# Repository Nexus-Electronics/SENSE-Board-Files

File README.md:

# SENSE-Board-Files

This repository contains the EAGLE files for SENSE.

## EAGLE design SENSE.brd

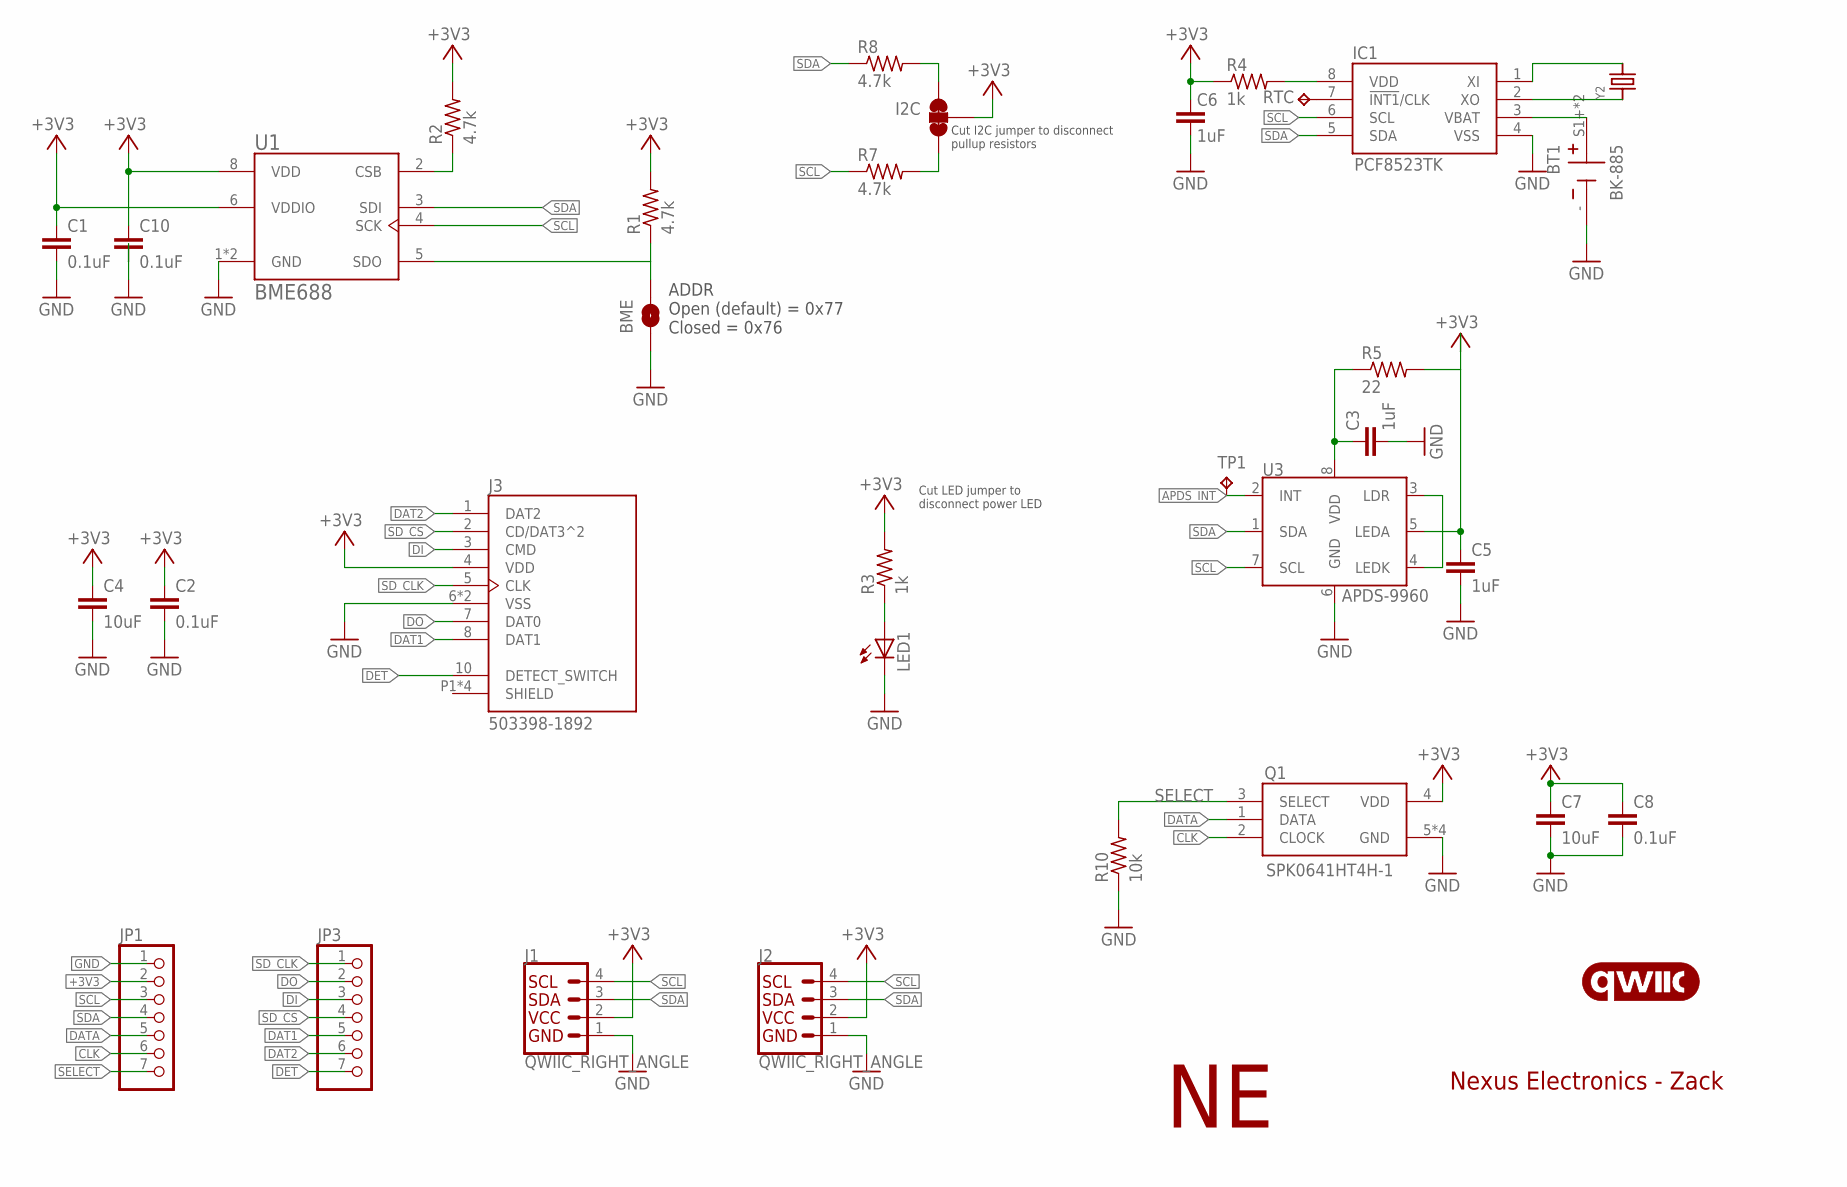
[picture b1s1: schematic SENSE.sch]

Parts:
BME: JUMPER-SMT_2_NO_SILK; SMT-JUMPER_2_NO_SILK
BT1: BK-885; BAT_BK-885
C1, C2, C8, C10: 0.1uF; 0603-1608X90N
C3, C5, C6: 1uF; 0603-1608X90N
C4, C7: 10uF; 0603-1608X90N
I2C: JUMPER-SMT_3_2-NC_TRACE_SILK; SMT-JUMPER_3_2-NC_TRACE_SILK
IC1: PCF8523TK; SON80P400X400X100-9N
J1, J2: QWIIC_RIGHT_ANGLE; JST04_1MM_RA
J3: 503398-1892; MOLEX_503398-1892
JP1, JP3: MICROBUILDER_HEADER-1X12; MICROBUILDER_1X12_ROUND
LED1: LED_GREENCHIP-LED0603; ADAFRUIT_CHIP-LED0603
LOGO1: QWIIC_LOGO_CONNECTOR; QWIIC_5.5MM
Q1: SPK0641HT4H-1; SPK0641HT4H1
R1, R2, R7, R8: 4.7k; 0603-1608X90N
R3, R4: 1k; 0603-1608X90N
R5: 22; 0603-1608X90N
R10: 10k; 0603-1608X90N
RTC: TPB2,54; B2,54
TP1: TPB2,54; B2,54
U1: BME688; PSON80P300X300X100-8N
U3: APDS-9960
Y2: MICROBUILDER_CRYSTAL_3215; MICROBUILDER_XTAL3215

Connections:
+3V3: C1.1, C2.1, C4.1, C5.1, C6.1, C7.1, C8.1, C10.1, I2C.2, J1.2, J2.2, J3.4 (VDD), JP1.2, Q1.4 (VDD), R1.2, R2.2, R3.2, R4.1, R5.2, U1.6 (VDDIO), U1.8 (VDD), U3.5 (LEDA)
APDS_INT: TP1.TP, U3.2 (INT)
CLK: JP1.6, Q1.2 (CLOCK)
CS: R2.1, U1.2 (CSB)
DAT1: J3.8 (DAT1), JP3.5
DAT2: J3.1 (DAT2), JP3.6
DATA: JP1.5, Q1.1 (DATA)
DET: J3.10 (DETECT_SWITCH), JP3.7
DI: J3.3 (CMD), JP3.3
DO: J3.7 (DAT0), JP3.2
GND: BME.1, BT1.-, C1.2, C2.2, C3.2, C4.2, C5.2, C6.2, C7.2, C8.2, C10.2, IC1.4 (VSS), J1.1, J2.1, J3.6 (VSS), J3.9 (VSS), JP1.1, LED1.C, Q1.5 (GND), Q1.6 (GND), Q1.7 (GND), Q1.8 (GND), R10.1, U1.1 (GND), U1.7 (GND), U3.6 (GND)
unnamed: C3.1, R5.1, U3.8 (VDD)
unnamed: IC1.2 (XO), Y2.P$1 (1)
unnamed: BT1.S1+ (+), BT1.S2+ (+), IC1.3 (VBAT)
unnamed: IC1.1 (XI), Y2.P$2 (2)
unnamed: LED1.A, R3.1
unnamed: IC1.7 (!INT1!/CLK), RTC.TP
unnamed: IC1.8 (VDD), R4.2
unnamed: I2C.1, R8.2
unnamed: I2C.3, R7.2
unnamed: U3.3 (LDR), U3.4 (LEDK)
SCL: IC1.6 (SCL), J1.4, J2.4, JP1.3, R7.1, U1.4 (SCK), U3.7 (SCL)
SDA: IC1.5 (SDA), J1.3, J2.3, JP1.4, R8.1, U1.3 (SDI), U3.1 (SDA)
SDO/ADR: BME.2, R1.1, U1.5 (SDO)
SD_CLK: J3.5 (CLK), JP3.1
SD_CS: J3.2 (CD/DAT3^2), JP3.4
SELECT: JP1.7, Q1.3 (SELECT), R10.2

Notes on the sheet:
ADDR Open (default) = 0x77 Closed = 0x76
Cut I2C jumper to disconnect pullup resistors
Cut LED jumper to disconnect power LED
Nexus Electronics - Zack

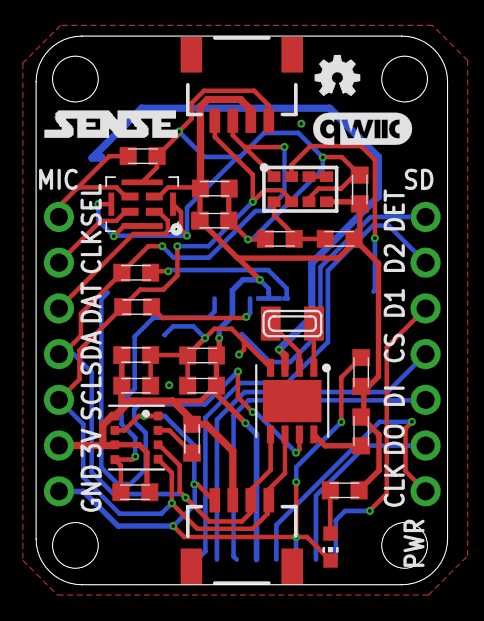
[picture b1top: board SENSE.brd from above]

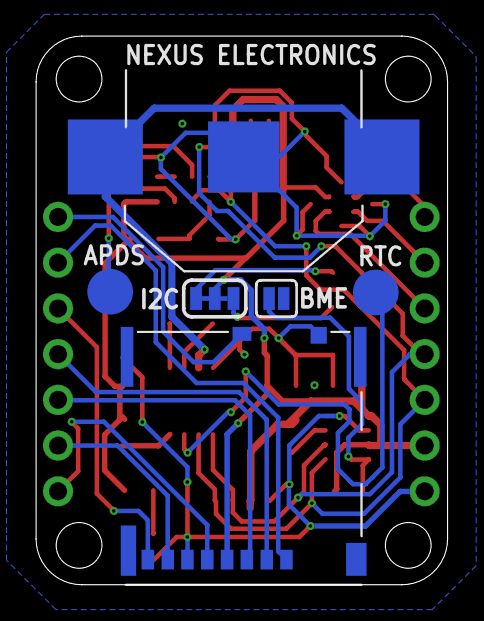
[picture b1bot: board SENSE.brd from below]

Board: 2 copper layers, 22.9 x 30.5 mm, 35 parts (6 on the bottom side), 27 nets.

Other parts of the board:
U$2: OSHW-LOGO-MINI

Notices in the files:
parts and their libraries:
SparkFun-Aesthetics: Licensing: Creative Commons ShareAlike 4.0 International - https://creativecommons.org/licenses/by-sa/4.0
